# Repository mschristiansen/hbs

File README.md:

Controller for the Harley Brewing System
========================================

Install Dependencies
--------------------

Requires `avrdude` and `gcc-avr`.

```
$ sudo apt install arduino-mk
```

Initialise git submodules to fetch source code for display and
temperature sensor (installed in `firmware/lib`).

```
$ git submodule init
```

Compile and Upload Firmware
---------------------------

The firmware was tested with Arduino UNO and Arduino Pro Mini. Both of
these boards will auto reset i.e. no need to manually reset before
upload.

Change port and baud rate in `firmware/Makefile` according to
board. The Arduino UNO is generally on port `/dev/ttyACM0` and can
handle speeds up to 115200 baud. The Arduino Pro Mini is generally on
port `/dev/ttyUSB0` and can only handle speeds up to 57600 baud.

```
$ make upload
```

References
----------

- http://www.nongnu.org/avr-libc/user-manual/index.html
- http://playground.arduino.cc/Learning/OneWire

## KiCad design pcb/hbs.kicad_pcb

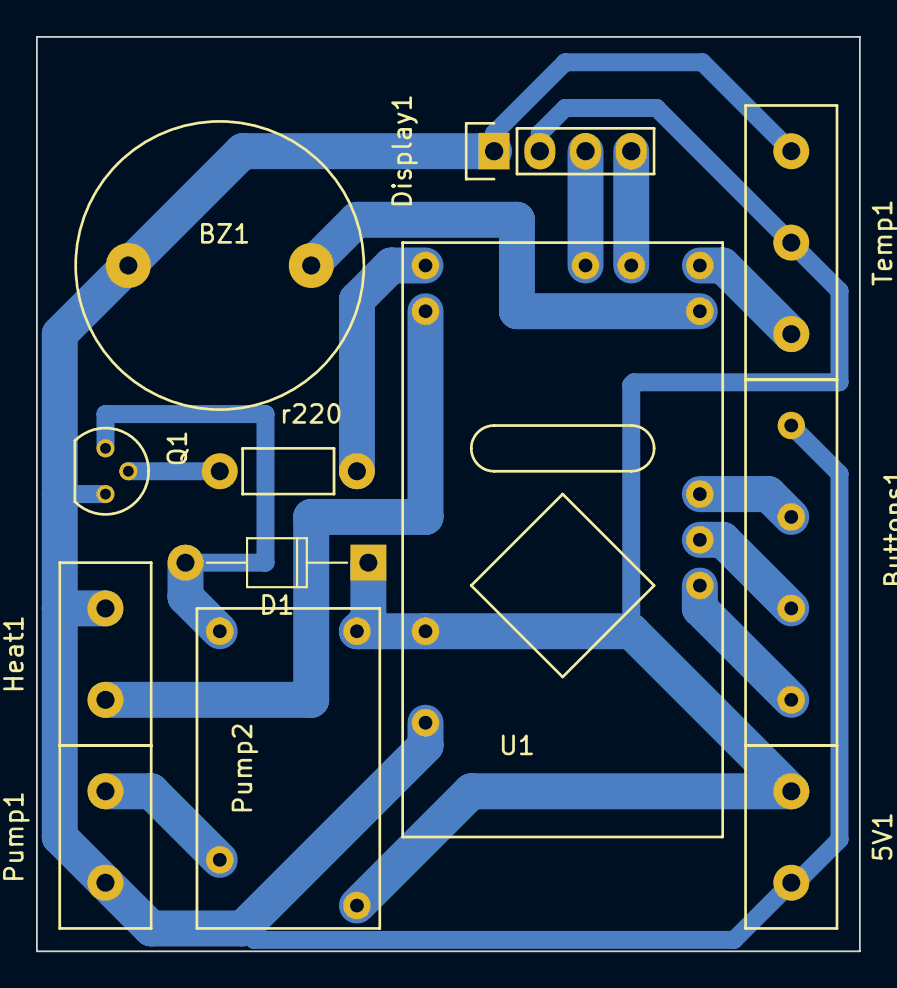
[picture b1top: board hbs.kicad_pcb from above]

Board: 2 copper layers, 45.7 x 50.8 mm, 12 parts (0 on the bottom side), 14 nets.

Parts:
5V1: Screw_Terminal_01x02; screw-terminal-2-5.08
BZ1: Buzzer; BUZZER
Buttons1: Conn_01x04; screw-terminal-4-5.08
D1: 1N4148; D_T-1_P10.16mm_Horizontal
Display1: JST Conn; Pin_Header_Straight_1x04
Heat1: Screw_Terminal_01x02; screw-terminal-2-5.08
Pump1: Screw_Terminal_01x02; screw-terminal-2-5.08
Pump2: FINDER-36.11-4301; relay-OJE-SS-105HM
Q1: BC337; TO-92_Molded_Narrow
Temp1: Screw_Terminal_01x03; screw-terminal-3-5.08
U1: RobotDynProMini
r220: R; Resistor_Horizontal_RM7mm

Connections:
GND: 5V1.1, BZ1.1, Buttons1.1, Display1.1, Heat1.1, Pump1.1, Q1.3, Temp1.1, U1.GND
unnamed: BZ1.2, U1.D8
unnamed: Buttons1.2, U1.D4
unnamed: Buttons1.3, U1.D3
unnamed: Buttons1.4, U1.D2
unnamed: D1.2, Pump2.A1, Q1.1
unnamed: Display1.3, U1.A5
unnamed: Display1.4, U1.A4
unnamed: Heat1.2, U1.D11
unnamed: Pump1.2, Pump2.14
unnamed: Q1.2, r220.1
unnamed: Temp1.3, U1.D9
unnamed: U1.D10, r220.2
VCC: 5V1.2, D1.1, Display1.2, Pump2.11, Pump2.A2, Temp1.2, U1.VCC

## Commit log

2017-08-30 Included libs for OLED display
2017-08-30 Rename led to Main
2017-08-30 Can display temperature
2017-08-30 Add PID controller module.
2017-08-30 Add hardware description
2017-09-05 Add button interrupts
2017-09-05 Remove unused argument from temp_init()
2017-09-05 Set port to /dev/ttyACM0 in Makefile
2017-09-05 Move source files to src/ directory
2017-09-23 Add module for buzzer
2017-09-23 Documentation update. Add requirements.
2017-09-23 Use shared header file
2017-09-23 Started menu control
2017-09-23 Simple menu control working
2017-09-23 Comment out serial.print commands in temperature module
2017-09-23 Update docs on temperature probe
2017-09-23 Integrated PID controller, but not yet working
2017-09-23 Can switch heater between off and pwm
2017-09-26 Use wildcard to simplify makefile for creating object files
2017-10-03 Adds hardware
2017-10-06 Move firmware source code to firmware directory
2017-10-07 Add datasheet for temperature sensor
2017-10-10 Refactor temperature and buttons. Add buzzer to display.
2017-10-16 Update README on flashing the firmware
2017-10-16 Use simpler control algorithm for temperature control
2017-11-07 Add KiCAD files for RobotDyn PCB
2017-11-08 Change relay footprint and cosmetic changes to schematic
2017-11-09 Change firmware to support more temperature sensors
2017-11-09 Add pull-up resistor for temperature sensor to schematic
